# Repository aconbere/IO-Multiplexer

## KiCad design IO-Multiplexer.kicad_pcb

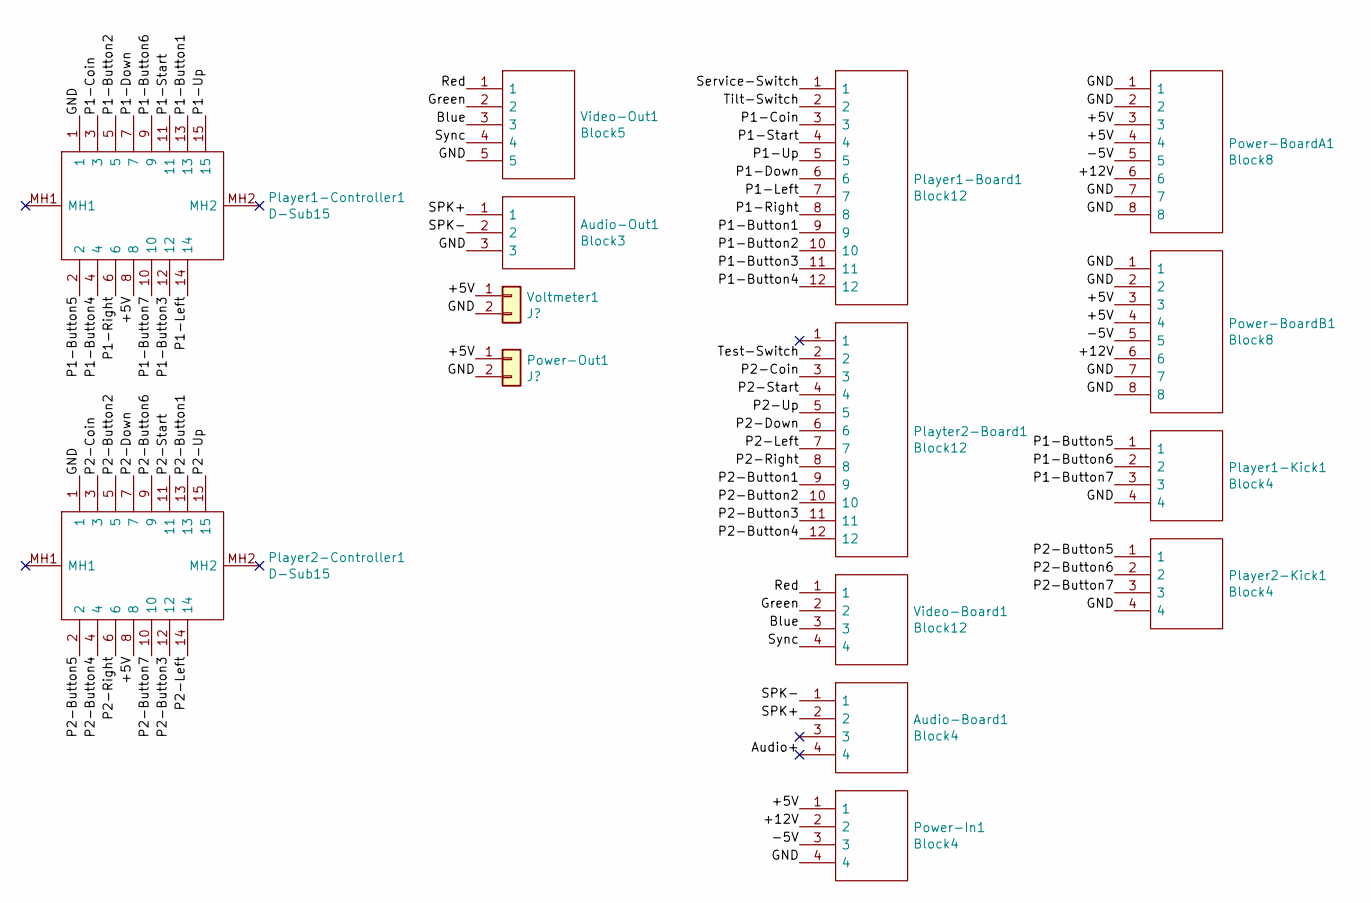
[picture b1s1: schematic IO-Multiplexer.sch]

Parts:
Audio-Board1: Block4; TB00150004BE; Mouser Part Number 490-TB001-500-04BE
Audio-Out1: Block3; SHDR3W100P0X500_1X3_1500X900X1290P; Mouser Part Number 490-TB001-500-03BE
Player1-Board1: Block12; SHDR12W100P0X500_1X12_6000X900X1250P; Mouser Part Number 490-TB001-500-12BE
Player1-Controller1, Player2-Controller1: D-Sub15; D15P33E4PA00LF; Mouser Part Number 649-D15P33E4PA00LF
Player1-Kick1, Player2-Kick1: Block4; TB00150004BE; Mouser Part Number 490-TB001-500-04BE
Playter2-Board1: Block12; SHDR12W100P0X500_1X12_6000X900X1250P; Mouser Part Number 490-TB001-500-12BE
Power-BoardA1: Block8; TB00150008BE; Mouser Part Number 490-TB001-500-08BE
Power-BoardB1: Block8; TB00150008BE; Mouser Part Number 490-TB001-500-08BE
Power-In1: Block4; TB00150004BE; Mouser Part Number 490-TB001-500-04BE
Power-Out1: J?; JST_EH_B2B-EH-A_1x02_P2.50mm_Vertical
Video-Board1: Block12; TB00150004BE; Mouser Part Number 490-TB001-500-04BE
Video-Out1: Block5; TB003500P05BE; Mouser Part Number 490-TB003-500-P05BE
Voltmeter1: J?; JST_EH_B2B-EH-A_1x02_P2.50mm_Vertical

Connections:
/+5V: Player1-Controller1.8, Player2-Controller1.8, Power-BoardA1.3, Power-BoardA1.4, Power-BoardB1.3, Power-BoardB1.4, Power-In1.1, Power-Out1.1, Voltmeter1.1
/+12V: Power-BoardA1.6, Power-BoardB1.6, Power-In1.2
/-5V: Power-BoardA1.5, Power-BoardB1.5, Power-In1.3
/Audio+: Audio-Board1.4
/Blue: Video-Board1.3, Video-Out1.3
/GND: Audio-Out1.3, Player1-Controller1.1, Player1-Kick1.4, Player2-Controller1.1, Player2-Kick1.4, Power-BoardA1.1, Power-BoardA1.2, Power-BoardA1.7, Power-BoardA1.8, Power-BoardB1.1, Power-BoardB1.2, Power-BoardB1.7, Power-BoardB1.8, Power-In1.4, Power-Out1.2, Video-Out1.5, Voltmeter1.2
/Green: Video-Board1.2, Video-Out1.2
/P1-Button1: Player1-Board1.9, Player1-Controller1.13
/P1-Button2: Player1-Board1.10, Player1-Controller1.5
/P1-Button3: Player1-Board1.11, Player1-Controller1.12
/P1-Button4: Player1-Board1.12, Player1-Controller1.4
/P1-Button5: Player1-Controller1.2, Player1-Kick1.1
/P1-Button6: Player1-Controller1.9, Player1-Kick1.2
/P1-Button7: Player1-Controller1.10, Player1-Kick1.3
/P1-Coin: Player1-Board1.3, Player1-Controller1.3
/P1-Down: Player1-Board1.6, Player1-Controller1.7
/P1-Left: Player1-Board1.7, Player1-Controller1.14
/P1-Right: Player1-Board1.8, Player1-Controller1.6
/P1-Start: Player1-Board1.4, Player1-Controller1.11
/P1-Up: Player1-Board1.5, Player1-Controller1.15
/P2-Button1: Player2-Controller1.13, Playter2-Board1.9
/P2-Button2: Player2-Controller1.5, Playter2-Board1.10
/P2-Button3: Player2-Controller1.12, Playter2-Board1.11
/P2-Button4: Player2-Controller1.4, Playter2-Board1.12
/P2-Button5: Player2-Controller1.2, Player2-Kick1.1
/P2-Button6: Player2-Controller1.9, Player2-Kick1.2
/P2-Button7: Player2-Controller1.10, Player2-Kick1.3
/P2-Coin: Player2-Controller1.3, Playter2-Board1.3
/P2-Down: Player2-Controller1.7, Playter2-Board1.6
/P2-Left: Player2-Controller1.14, Playter2-Board1.7
/P2-Right: Player2-Controller1.6, Playter2-Board1.8
/P2-Start: Player2-Controller1.11, Playter2-Board1.4
/P2-Up: Player2-Controller1.15, Playter2-Board1.5
/Red: Video-Board1.1, Video-Out1.1
/SPK+: Audio-Board1.2, Audio-Out1.1
/SPK-: Audio-Board1.1, Audio-Out1.2
/Service-Switch: Player1-Board1.1
/Sync: Video-Board1.4, Video-Out1.4
/Test-Switch: Playter2-Board1.2
/Tilt-Switch: Player1-Board1.2

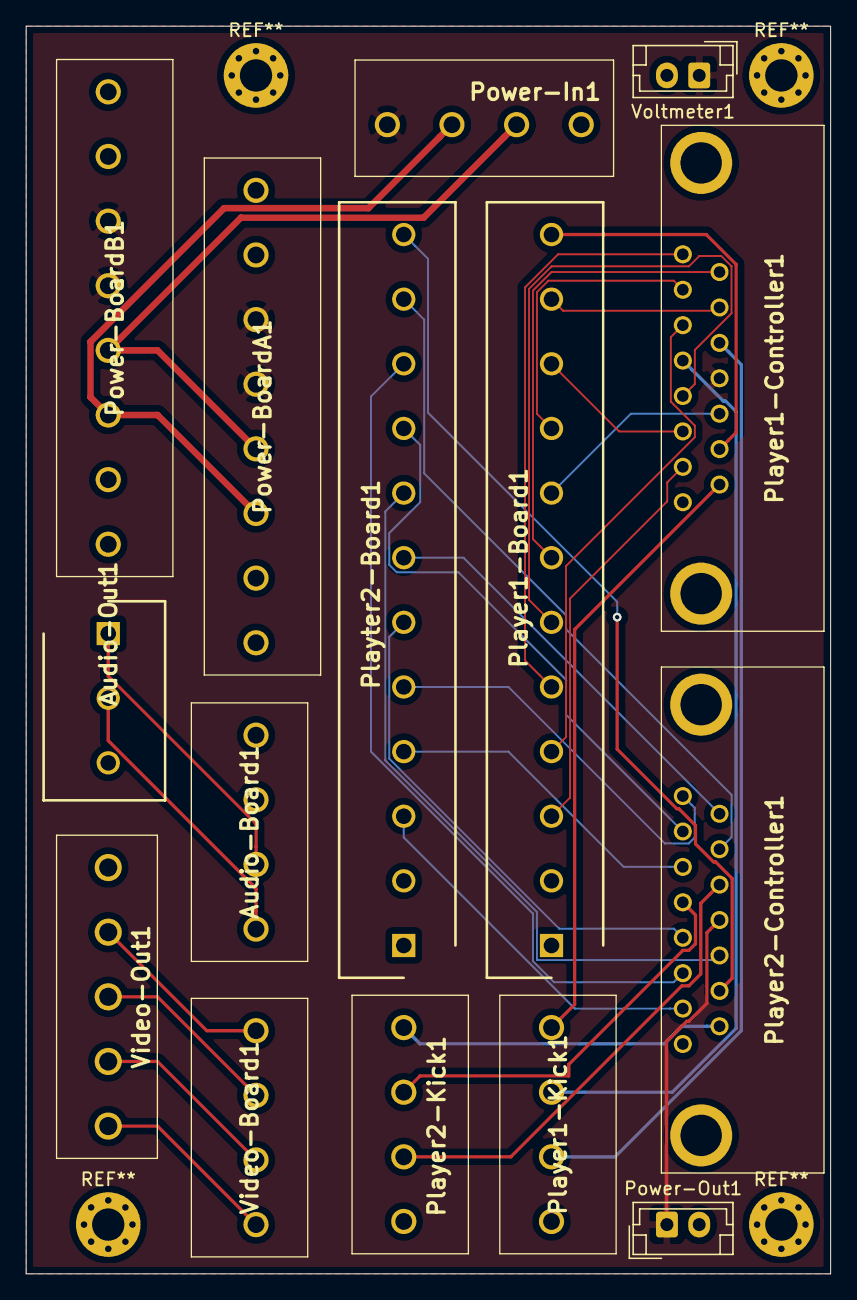
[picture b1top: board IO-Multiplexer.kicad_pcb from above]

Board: 2 copper layers, 62.2 x 96.5 mm, 15 parts (0 on the bottom side), 36 nets.

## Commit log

2020-07-31 Reroute
2020-08-02 Fully routed P1 controls
    Making more efficient use of traces
2020-08-02 Fix a DRC error, via too close to track
2020-08-02 Rerouted all controls
2020-08-02 add b.silk text
2020-09-23 Update to neo-geo plus pinout
2020-09-23 Connecting 5V to P2 since the zone wont fill there
